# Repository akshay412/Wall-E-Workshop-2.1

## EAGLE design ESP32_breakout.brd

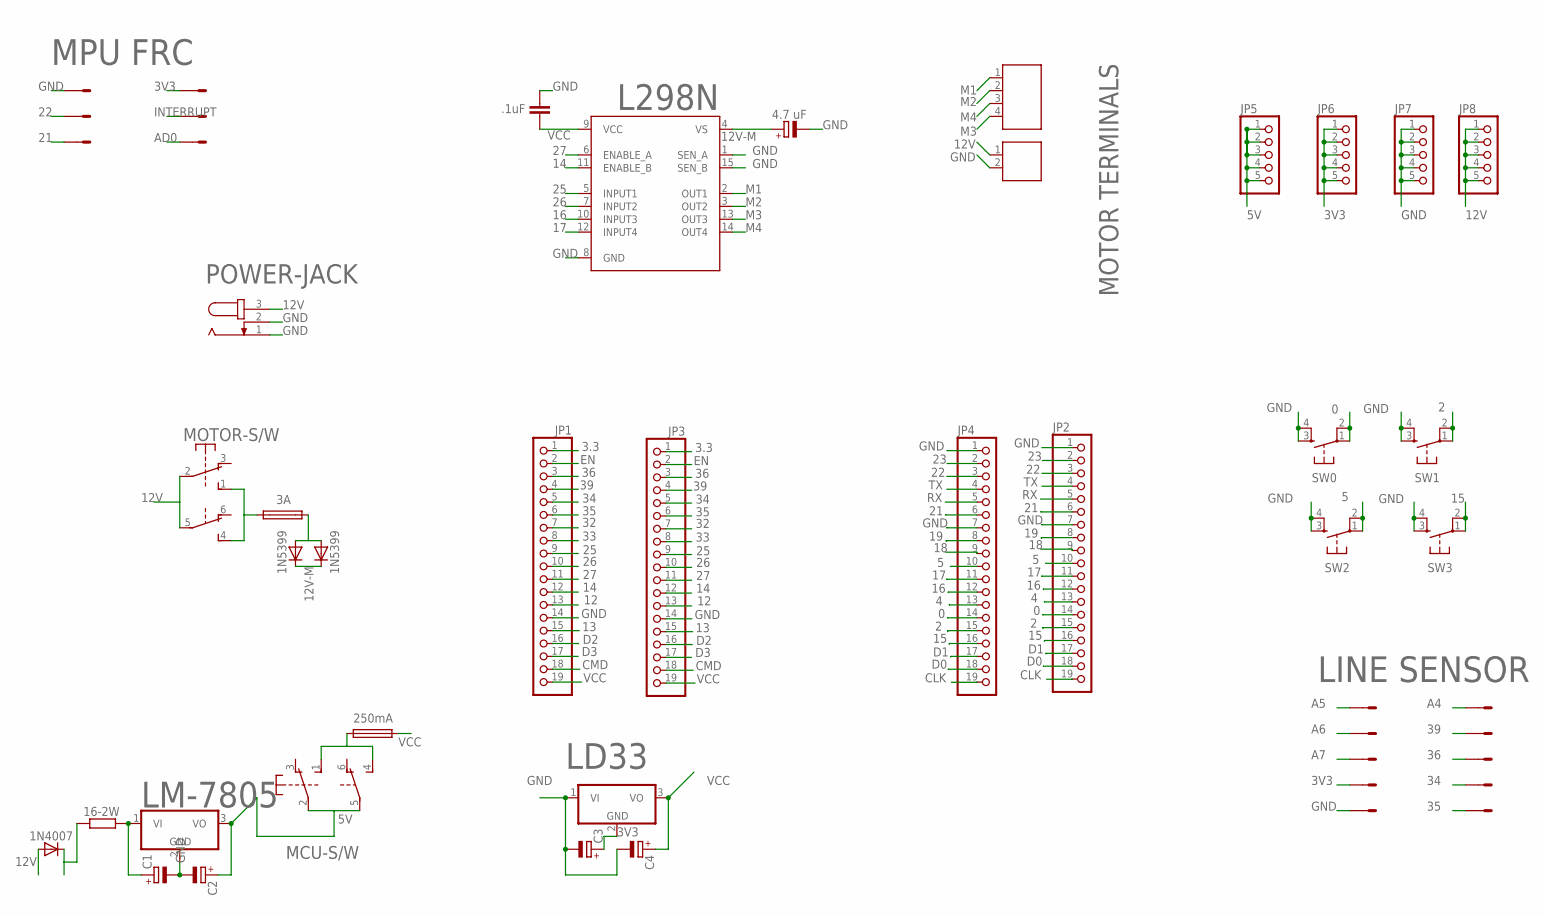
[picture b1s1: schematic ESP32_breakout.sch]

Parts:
12V: 691131710002
16-2W: R-EU_0617/17; 0617/17
C1, C2, C3, C4: CPOL-EUE2.5-6; E2,5-6
C8: 4.7 uF; E2,5-6
C9: .1uF; C5B2.5
D4: 1N4007; D-7.5
D6, D7: 1N5399; DO15-12
F1: 3A; SH25
F2: 250mA; SH25
J1: 691131710004
JP1, JP2, JP3, JP4: PINHD-1X19; 1X19
JP5, JP6, JP7, JP8: PINHD-1X5; 1X05
L298N: L298; MULTIWATT-15
LD33: 786TV; TO220V
LINE-SENSOR: 057-010-1
LM-7805: 786TV; TO220V
MCU-S/W: 9077-2
MOTOR-S/W: 9077-2
MPU-6050: 057-006-1
POWER-JACK: JACK-PLUG1; SPC4078
SW0, SW1, SW2, SW3: DTS-6

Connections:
0: JP2.14, JP4.14, SW0.1, SW0.2
2: JP2.15, JP4.15, SW1.1, SW1.2
3.3: JP1.1, JP3.1
3V3: C3.+, JP6.1, JP6.2, JP6.3, JP6.4, JP6.5, LD33.2 (GND), LINE-SENSOR.7, MPU-6050.2
4: JP2.13, JP4.13
5: JP2.10, JP4.10, SW2.1, SW2.2
5V: C2.+, JP5.1, JP5.2, JP5.3, JP5.4, JP5.5, LM-7805.3 (VO), MCU-S/W.2, MCU-S/W.5
12: JP1.13, JP3.13
12V: 12V.1, D4.A, JP8.1, JP8.2, JP8.3, JP8.4, JP8.5, MOTOR-S/W.2, MOTOR-S/W.5, POWER-JACK.3
12V-M: C8.+, D6.C, D7.C, L298N.4 (VS)
13: JP1.15, JP3.15
14: JP1.12, JP3.12, L298N.11 (ENABLE_B)
15: JP2.16, JP4.16, SW3.1, SW3.2
16: JP2.12, JP4.12, L298N.10 (INPUT3)
17: JP2.11, JP4.11, L298N.12 (INPUT4)
18: JP2.9, JP4.9
19: JP2.8, JP4.8
21: JP2.6, JP4.6, MPU-6050.5
22: JP2.3, JP4.3, MPU-6050.3
23: JP2.2, JP4.2
25: JP1.9, JP3.9, L298N.5 (INPUT1)
26: JP1.10, JP3.10, L298N.7 (INPUT2)
27: JP1.11, JP3.11, L298N.6 (ENABLE_A)
32: JP1.7, JP3.7
33: JP1.8, JP3.8
34: JP1.5, JP3.5, LINE-SENSOR.8
35: JP1.6, JP3.6, LINE-SENSOR.10
36: JP1.3, JP3.3, LINE-SENSOR.6
39: JP1.4, JP3.4, LINE-SENSOR.4
A4: LINE-SENSOR.2
A5: LINE-SENSOR.1
A6: LINE-SENSOR.3
A7: LINE-SENSOR.5
CLK: JP2.19, JP4.19
CMD: JP1.18, JP3.18
D0: JP2.18, JP4.18
D1: JP2.17, JP4.17
D2: JP1.16, JP3.16
D3: JP1.17, JP3.17
EN: JP1.2, JP3.2
GND: 12V.2, C1.-, C2.-, C3.-, C4.-, C8.-, C9.2, JP1.14, JP2.1, JP2.7, JP3.14, JP4.1, JP4.7, JP7.1, JP7.2, JP7.3, JP7.4, JP7.5, L298N.1 (SEN_A), L298N.8 (GND), L298N.15 (SEN_B), LD33.1 (VI), LINE-SENSOR.9, LM-7805.2 (GND), MPU-6050.1, MPU-6050.6, POWER-JACK.1, POWER-JACK.2, SW0.3, SW0.4, SW1.3, SW1.4, SW2.3, SW2.4, SW3.3, SW3.4
INTERRUPT: MPU-6050.4
M1: J1.1, L298N.2 (OUT1)
M2: J1.2, L298N.3 (OUT2)
M3: J1.4, L298N.13 (OUT3)
M4: J1.3, L298N.14 (OUT4)
unnamed: 16-2W.2, C1.+, LM-7805.1 (VI)
unnamed: F1.1, MOTOR-S/W.1 (S), MOTOR-S/W.4 (S)
unnamed: F2.1, MCU-S/W.1 (S), MCU-S/W.4 (S)
unnamed: 16-2W.1, D4.C
unnamed: D6.A, D7.A, F1.2
RX: JP2.5, JP4.5
TX: JP2.4, JP4.4
VCC: C4.+, C9.1, F2.2, JP1.19, JP3.19, L298N.9 (VCC), LD33.3 (VO)

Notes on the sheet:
LINE SENSOR
MOTOR TERMINALS
MPU FRC
AD0

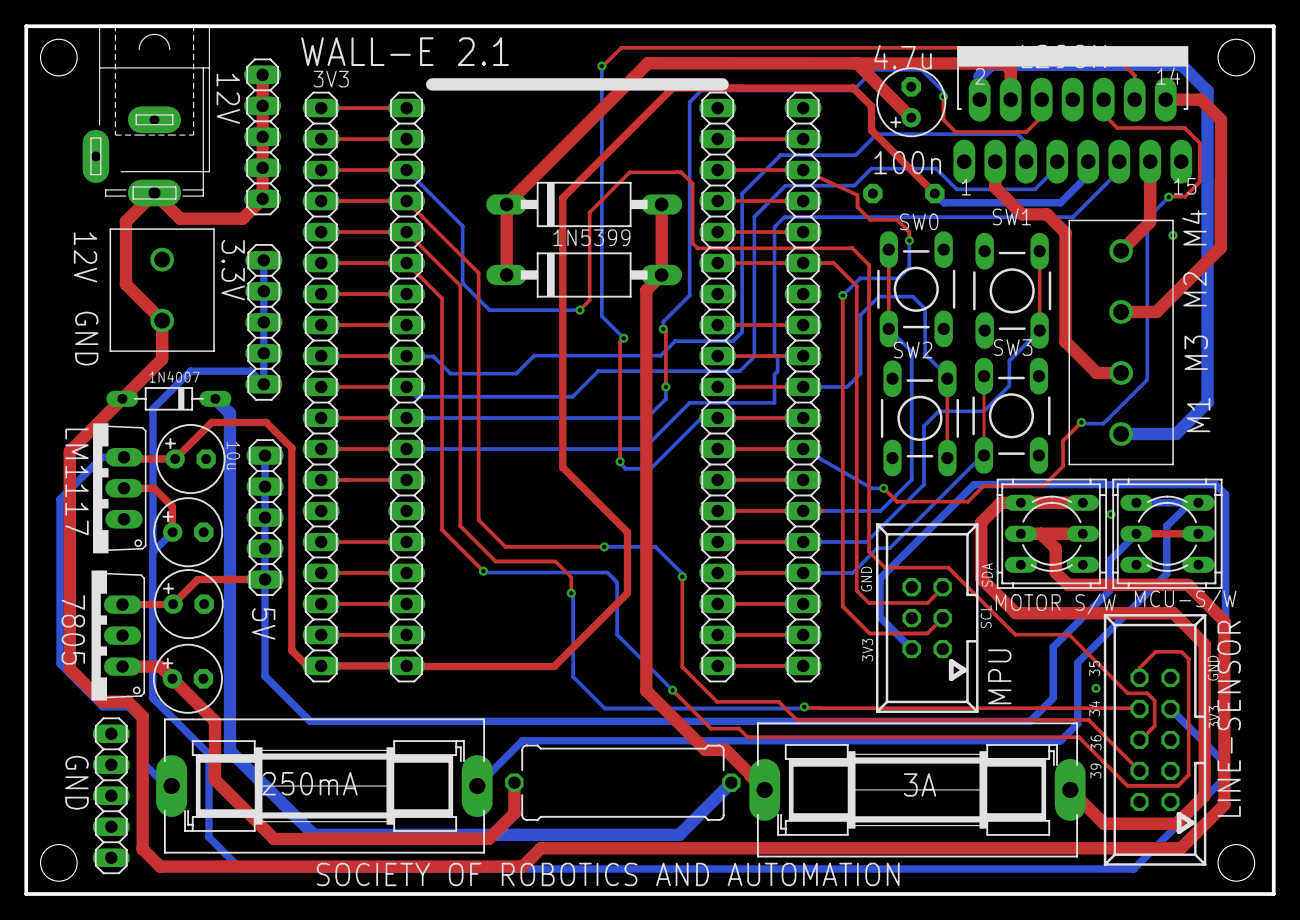
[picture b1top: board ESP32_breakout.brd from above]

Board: 2 copper layers, 102.2 x 71.1 mm, 34 parts (1 on the bottom side), 49 nets.

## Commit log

2020-01-28 Added board files

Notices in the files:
parts and their libraries:
Wurth_Elektronik_Electromechanic_Termina: Copyright: Würth Elektronik
